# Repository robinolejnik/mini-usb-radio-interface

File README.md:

# mini-usb-radio-interface

A small CM108 USB radio interface providing audio, PTT and Squelch lines. PCB fits into a 9 pin D-Sub connector.

[View the interactive BOM](https://htmlpreview.github.io/?https://github.com/robinolejnik/mini-usb-radio-interface/blob/main/ibom.html)

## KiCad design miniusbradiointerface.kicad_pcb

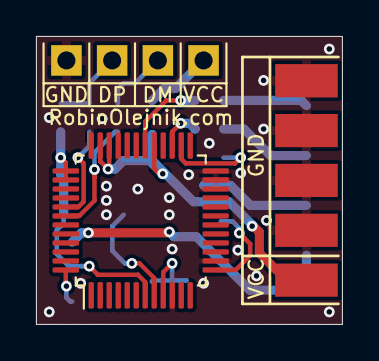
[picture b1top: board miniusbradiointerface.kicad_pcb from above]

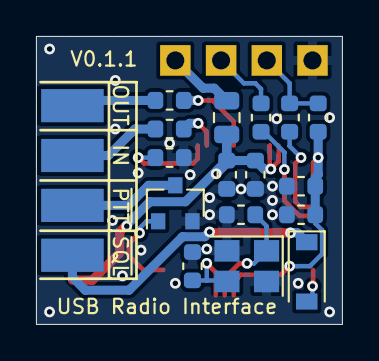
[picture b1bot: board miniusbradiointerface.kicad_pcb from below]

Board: 2 copper layers, 17.0 x 16.0 mm, 22 parts (16 on the bottom side), 19 nets.

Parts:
C1, C2: 20p; C_0603_1608Metric
C3, C5: 100n; C_0603_1608Metric
C4, C6, C7: 4.7u; C_0603_1608Metric
C8, C9: 1u; C_0603_1608Metric
D1: B5819W(BAT46W); D_SOD-123
J1: VCC; PinHeader_1x01_P2.54mm_Vertical
J2: DP; PinHeader_1x01_P2.54mm_Vertical
J3: DM; PinHeader_1x01_P2.54mm_Vertical
J4: GND; PinHeader_1x01_P2.54mm_Vertical
J5: DB9_Male; DSUB-9_Male_EdgeMount_P2.77mm
L1: 10u; L_0805_2012Metric
Q1: BSS138; SOT-23
R1, R3: 22; R_0603_1608Metric
R2: 1.5k; R_0603_1608Metric
U1: CM108AH; LQFP-48_7x7mm_P0.5mm
Y1: 12M; Crystal_SMD_3225-4Pin_3.2x2.5mm

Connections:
+3V3: C5.1, C6.1, R2.2, U1.7 (PWRSEL), U1.37 (REGV), U1.38 (MSEL)
AUDIO_IN: C9.1, J5.8
AUDIO_OUT: C8.1, J5.9
GND: C1.2, C2.2, C3.2, C4.2, C5.2, C6.2, C7.2, J4.1, J5.2, J5.3, J5.4, J5.5, Q1.2 (S), U1.10 (MODE), U1.14 (DVSS), U1.22 (ADSEL), U1.23 (TEST), U1.24 (AVSS), U1.33 (AVSS), U1.36 (DVSS), Y1.2, Y1.4
unnamed: D1.2 (A), U1.48 (VOLDN)
unnamed: J1.1, L1.2
unnamed: J2.1, R2.1, R3.2
unnamed: J3.1, R1.2
unnamed: Q1.1 (G), U1.13 (GPIO3)
unnamed: C7.1, U1.26 (BGREF)
unnamed: C8.2, U1.30 (LOL)
unnamed: C9.2, U1.27 (MICIN)
unnamed: R1.1, U1.42 (USBDM)
unnamed: R3.1, U1.41 (USBDP)
unnamed: C1.1, U1.8 (XI), Y1.1
unnamed: C2.1, U1.9 (XO), Y1.3
PTT: J5.7, Q1.3 (D)
SQUELCH: D1.1 (K), J5.6
VCC: C3.1, C4.1, J5.1, L1.1, U1.29 (AVDD), U1.34 (AVDD), U1.35 (DVDD)

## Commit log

2020-04-09 Added schematic and pcb.
2020-10-22 Properly archived symbols
2020-10-22 Added project name, github-link license and author to schematic sheet.
2020-10-22 Added schematic PDF
2020-10-22 Added interactive BOM
2020-10-22 Added link to directly open the interactive BOM.
2021-12-25 KiCad 6 migration
2024-05-01 Add LICENSE
2024-05-01 Update project to KiCad 8
    Some symbols and footprints were updated and/or renamed in the library.
    Update the symbols, keep the footprints. Fix ERC and DRC errors.
    Update website URL and version
    Update PDF schematic
    Update ibom, add config file

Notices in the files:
miniusbradiointerface.kicad_pcb:
License: MIT
